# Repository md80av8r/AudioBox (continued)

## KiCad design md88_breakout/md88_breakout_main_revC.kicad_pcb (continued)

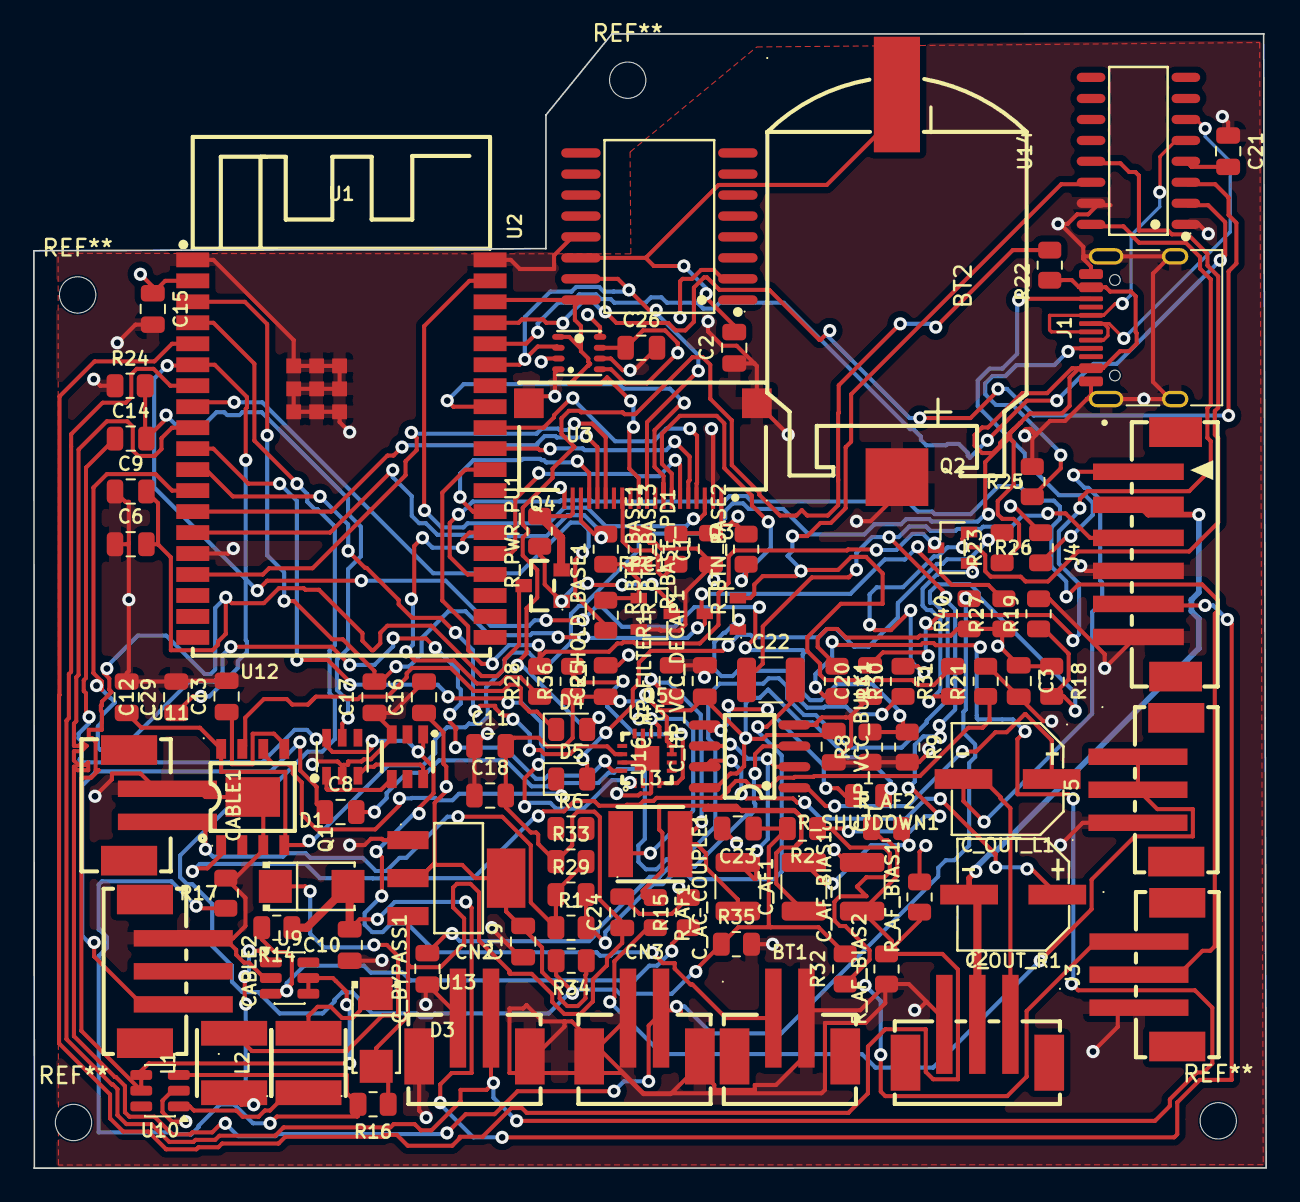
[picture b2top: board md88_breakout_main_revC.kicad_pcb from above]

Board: 4 copper layers, 74.6 x 68.7 mm, 108 parts (0 on the bottom side), 82 nets.

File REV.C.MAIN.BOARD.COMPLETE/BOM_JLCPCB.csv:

Comment,Designator,Footprint,LCSC Part #
18650_CELL,BT1,CONN-SMD_B2B-PH-SM4-TB-LF-SN,C160352
100nF,"C1,C2,C3,C14,C16,C20,C21,C23,C25,C26,C29,C_HP_VCC_DECAP1",C_0805_2012Metric,C49678
10uF,"C6,C9,C12,C13,C18,C_HP_VCC_BULK1",C_0805_2012Metric,C15850
1uF,"C8,C17,C_BYPASS1",C_0805_2012Metric,C28323
22uF,"C10,C11,C15,C19,C24",C_0805_2012Metric,C45783
10uF,"C22,C_AC_COUPLE1,C_AF1",C_1210_3225Metric,
MIC_PIGTAIL_0206,CABLE1,CONN-SMD_B2B-PH-SM4-TB-LF-SN,C160352
AUDIO_PIGTAIL_QUARTER_INCH,CABLE2,CONN-SMD_B3B-PH-SM4-TB-LF-SN,C160353
B2B-PH-SM4-TB,"CN2,CN3",CONN-SMD_B2B-PH-SM4-TB-LF-SN,C160352
100nF,C_AF_BIAS1,C_1210_3225Metric,
1nF,C_HP_FILTER1,C_0805_2012Metric,C46653
PM101M025E077PTR,"C_OUT_L1,C_OUT_R1",CAP-SMD_BD6.3-L6.6-W6.6-LS7.2-FD,C2858382
SS24,"D1,D3",SMA_L4.3-W2.6-LS5.2-RD,C50645
LED_CHRG_RED,D4,LED_0805_2012Metric,
LED_CHRG_GREEN,D5,LED_0805_2012Metric,
FH28K-20S-0.5SH,FPC1,CONN-SMD_FH28K-20S-0.5SH,C3168665
USB_C_POWER,J1,USB_C_Receptacle_HRO_TYPE-C-31-M-12,C165948
AUDIO_OUT_QUARTER_INCH,J2,CONN-SMD_B3B-PH-SM4-TB-LF-SN,C160353
MIC_OUT_0206,J3,CONN-SMD_B3B-PH-SM4-TB-LF-SN,C160353
LEMO_6PIN_PROFLIGHT,J4,CONN-SMD_6P-P2.00_B6B-PH-SM4-TB-LF-SN,C471518
AUX_IN_3.5MM,J5,CONN-SMD_B3B-PH-SM4-TB-LF-SN,C160353
4.7uH,"L1,L2",IND-SMD_L4.0-W4.0_LQH44PN2R2MP0L,C135263
SMNR4020-10UH,L3,IND-SMD_L4.0-W4.0_LQH44PN2R2MP0L,C135263
FS8205A_C2830320,Q1,SOT-23-6_L2.9-W1.6-P0.95-LS2.8-BR,C2830320
MMBT3904-C20526,"Q2,Q3,Q5",SOT-23-3_L2.9-W1.3-P1.90-LS2.4-BR,C20526
AO3401A,Q4,SOT-23_L2.9-W1.3-P1.90-LS2.4-BR,C15127
4.7k,"R1,R29",R_0805_2012Metric,C17673
10k,"R2,R15,R21,R27,R28,R30,R31,R32,R33,R40,R41,R_AF1,R_AF2,R_BASE_PD1,R_BTN_BASE1,R_BTN_BASE2,R_BTN_BASE3,R_HOLD_BASE1,R_PWR_PU1",R_0805_2012Metric,C17414
470,R6,R_0805_2012Metric,C17710
100k,"R8,R9,R18,R19,R34,R35,R36,R_AF_BIAS1,R_AF_BIAS2,R_SHUTDOWN1",R_0805_2012Metric,C17407
180k,R14,R_0805_2012Metric,C22827
200k,R16,R_0805_2012Metric,C17539
27k,R17,R_0805_2012Metric,C17593
1k,"R22,R23",R_0805_2012Metric,C17513
100,R24,R_0805_2012Metric,C17408
5.1k,"R25,R26",R_0805_2012Metric,C27834
ESP32-WROVER-E-N8R8,U1,WIFI-SMD_ESP32-WROVER-IE8MB,C2973667
DS3231SN#_C722469,U2,SOIC-16_L10.3-W7.5-P1.27-LS10.3-BL,C722469
BME280,U3,LGA-8_BME280_BL,C92489
MT3608,"U9,U10",SOT-23-6,
TP4056,U11,ESOP-8_L4.9-W3.9-P1.27-LS6.0-BL-EP,C16581
DW01A_C351410,U12,SOT-23-6_L2.9-W1.6-P0.95-LS2.8-BL,C351410
AMS1117-3.3,U13,SOT-223-3_L6.5-W3.4-P2.30-LS7.0-BR,C6186
CH340C_C7464026,U14,SOP-16_L10.0-W3.9-P1.27-LS6.0-BL,C7464026
MAX98357AETE+T,U15,TQFN-16_L3.0-W3.0-P0.50-BL-EP1.5,C910544
TPA6111A2DR,U16,SOIC-8_L5.0-W4.0-P1.27-LS6.0-BL,C497472

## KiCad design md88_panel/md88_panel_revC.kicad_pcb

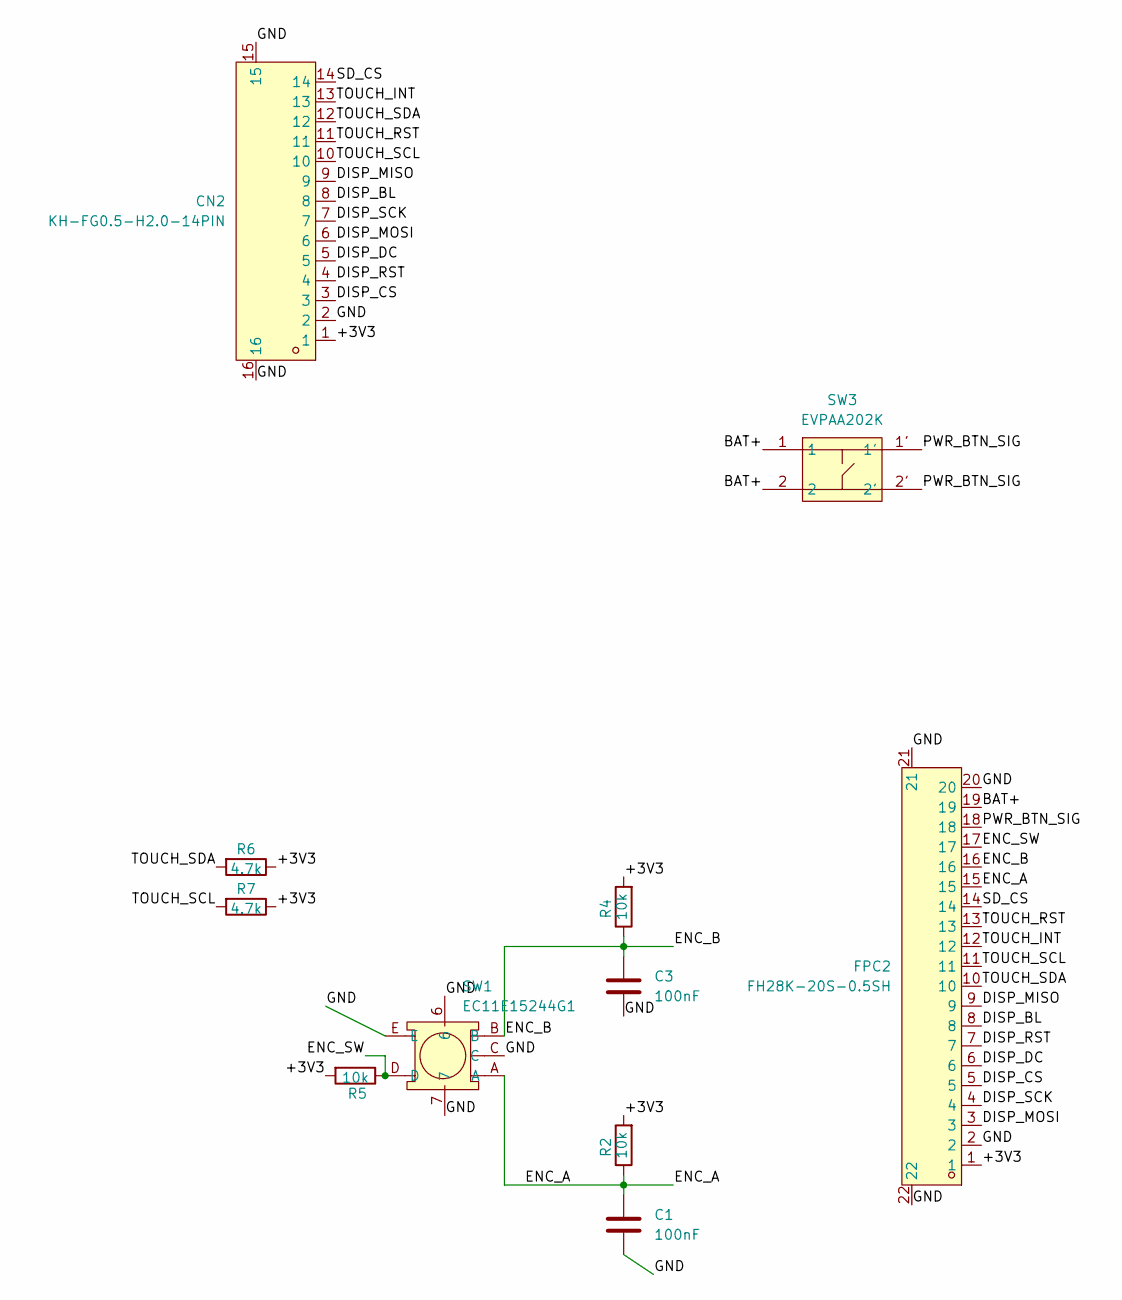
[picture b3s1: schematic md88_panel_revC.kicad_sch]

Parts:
C1, C3: 100nF; C_0805_2012Metric
CN2: KH-FG0.5-H2.0-14PIN; FPC-SMD_KH-FG0.5-H2.0-14PIN; MPN KH-FG0.5-H2.0-14PIN; LCSC Part C2797208
FPC2: FH28K-20S-0.5SH; CONN-SMD_FH28K-20S-0.5SH; MPN FH28K-20S-0.5SH; LCSC Part C3168665
R2, R4, R5: 10k; R_0805_2012Metric
R6, R7: 4.7k; R_0805_2012Metric
SW1: EC11E15244G1; SW-TH_EC11E15244G1; MPN EC11E15244G1; LCSC Part C370970
SW3: EVPAA202K; KEY-SMD_4P-L3.5-W2.9-P1.48-LS4.3-TL; MPN EVPAA202K; LCSC Part C79147

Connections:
/+3V3: CN2.1, FPC2.1, R2.2, R4.2, R5.2, R6.1, R7.1
/BAT+: FPC2.19, SW3.1, SW3.2
/DISP_BL: CN2.8, FPC2.8
/DISP_CS: CN2.3, FPC2.5
/DISP_DC: CN2.5, FPC2.6
/DISP_MISO: CN2.9, FPC2.9
/DISP_MOSI: CN2.6, FPC2.3
/DISP_RST: CN2.4, FPC2.7
/DISP_SCK: CN2.7, FPC2.4
/ENC_A: C1.1, FPC2.15, R2.1, SW1.A
/ENC_B: C3.1, FPC2.16, R4.1, SW1.B
/ENC_SW: FPC2.17, R5.1, SW1.D
/GND: C1.2, C3.2, CN2.2, CN2.15, CN2.16, FPC2.2, FPC2.20, FPC2.21, FPC2.22, SW1.6, SW1.7, SW1.C, SW1.E
/PWR_BTN_SIG: FPC2.18, SW3.1', SW3.2'
/SD_CS: CN2.14, FPC2.14
/TOUCH_INT: CN2.13, FPC2.12
/TOUCH_RST: CN2.11, FPC2.13
/TOUCH_SCL: CN2.10, FPC2.11, R7.2
/TOUCH_SDA: CN2.12, FPC2.10, R6.2

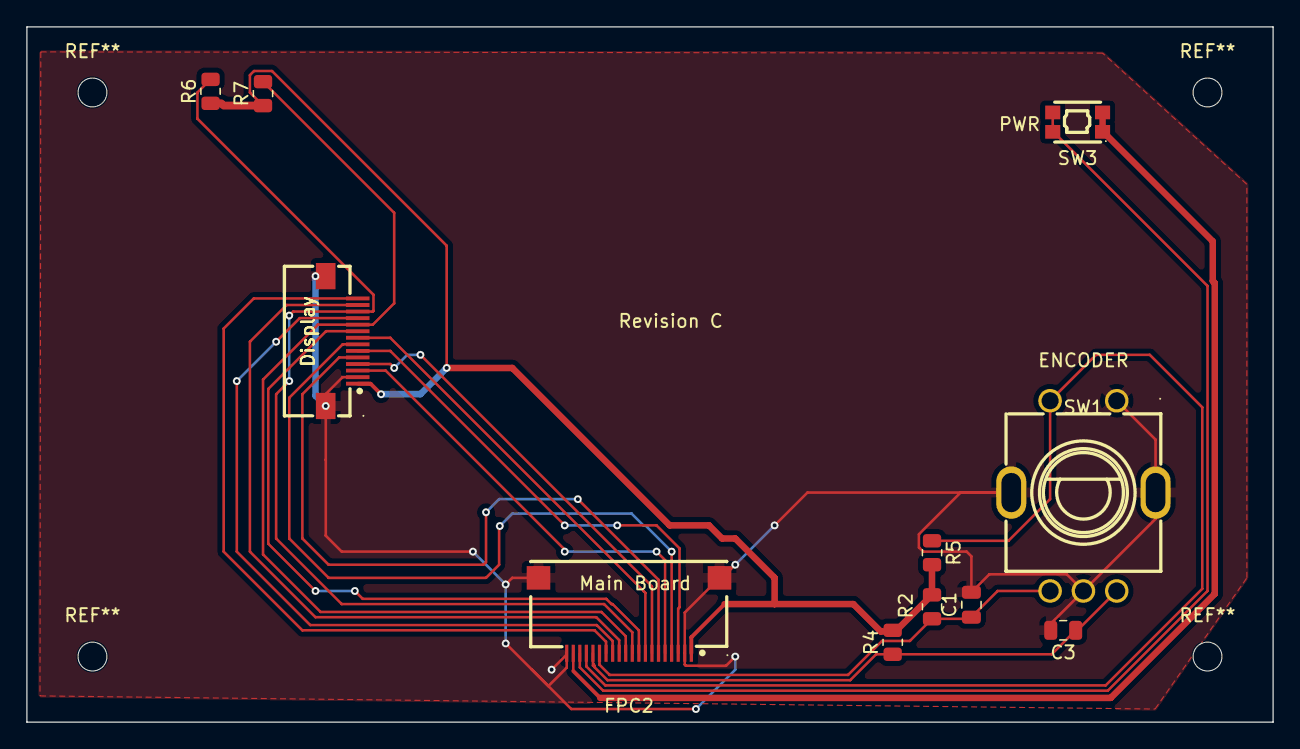
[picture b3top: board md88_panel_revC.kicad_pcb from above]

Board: 2 copper layers, 95.0 x 53.0 mm, 11 parts (0 on the bottom side), 19 nets.

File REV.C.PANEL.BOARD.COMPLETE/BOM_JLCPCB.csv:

Comment,Designator,Footprint,LCSC Part #
100nF,"C1,C3",C_0805_2012Metric,C49678
KH-FG0.5-H2.0-14PIN,CN2,FPC-SMD_KH-FG0.5-H2.0-14PIN,C2797208
FH28K-20S-0.5SH,FPC2,CONN-SMD_FH28K-20S-0.5SH,C3168665
10k,"R2,R4,R5",R_0805_2012Metric,C17414
4.7k,"R6,R7",R_0805_2012Metric,C17673
EC11E15244G1,SW1,SW-TH_EC11E15244G1,C370970
EVPAA202K,SW3,KEY-SMD_4P-L3.5-W2.9-P1.48-LS4.3-TL,C79147

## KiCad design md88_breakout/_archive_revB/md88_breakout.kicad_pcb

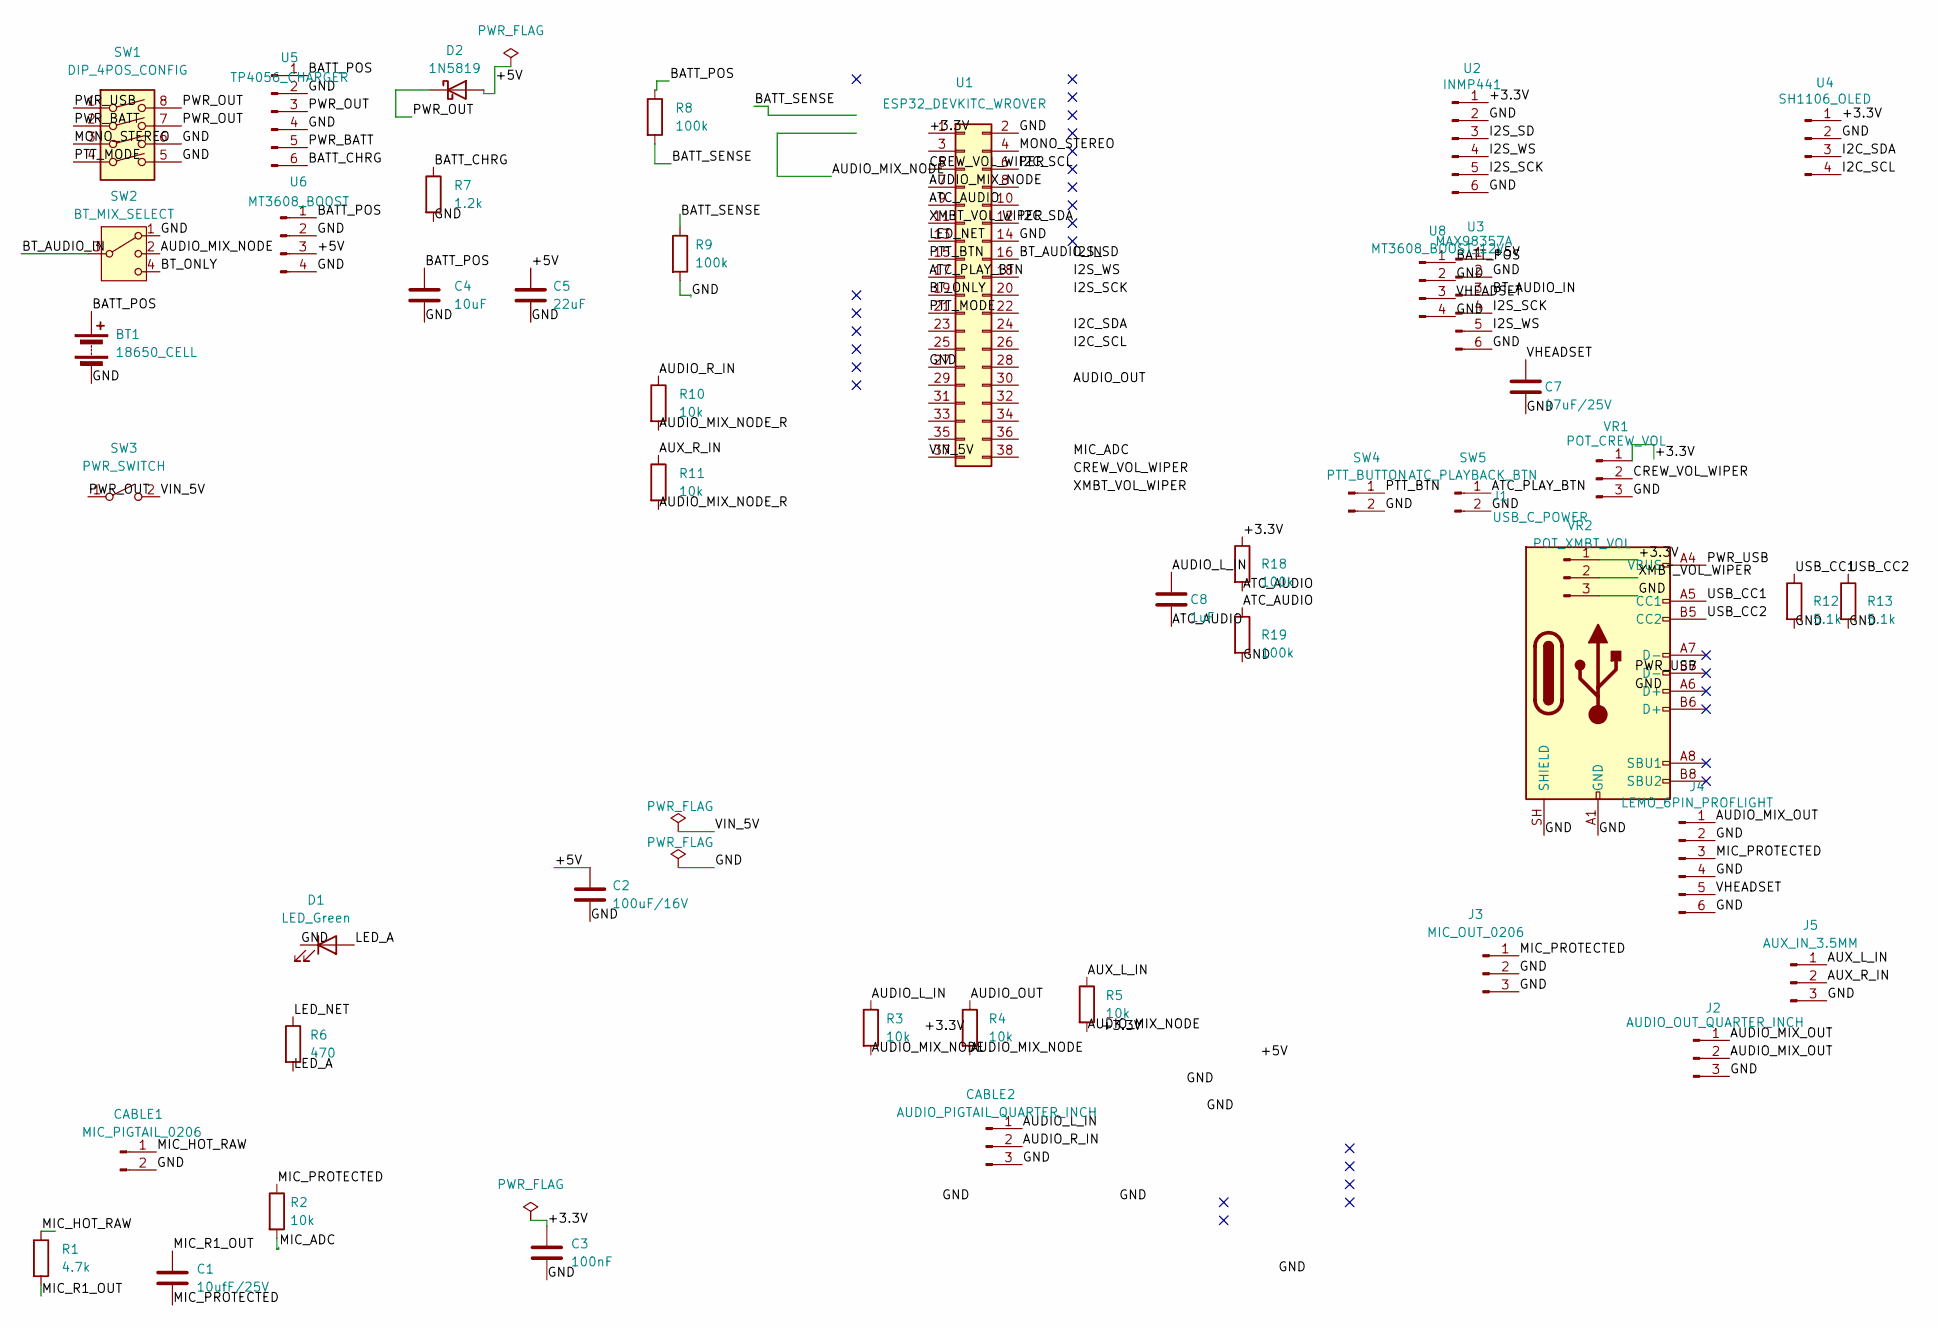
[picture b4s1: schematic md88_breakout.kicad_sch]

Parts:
BT1: 18650_CELL; BatteryHolder_Keystone_1042_1x18650
C1: 10ufF/25V; CP_Radial_D5.0mm_P2.00mm
C2: 100uF/16V; CP_Radial_D6.3mm_P2.50mm
C3: 100nF; C_0805_2012Metric
C4: 10uF; CP_Radial_D5.0mm_P2.00mm
C5: 22uF; CP_Radial_D6.3mm_P2.50mm
C7: 47uF/25V; CP_Radial_D6.3mm_P2.50mm
C8: 1uF; C_0805_2012Metric
CABLE1: MIC_PIGTAIL_0206; JST_PH_B2B-PH-K_1x02_P2.00mm_Vertical
CABLE2: AUDIO_PIGTAIL_QUARTER_INCH; JST_PH_B3B-PH-K_1x03_P2.00mm_Vertical
D1: LED_Green; LED_D3.0mm
D2: 1N5819; D_DO-41_SOD81_P10.16mm_Horizontal
J1: USB_C_POWER; USB_C_Receptacle_GCT_USB4105-xx-A_16P_TopMnt_Horizontal
J2: AUDIO_OUT_QUARTER_INCH; PinHeader_1x03_P2.54mm_Vertical
J3: MIC_OUT_0206; PinHeader_1x03_P2.54mm_Vertical
J4: LEMO_6PIN_PROFLIGHT; PinHeader_1x06_P2.54mm_Vertical
J5: AUX_IN_3.5MM; PinHeader_1x03_P2.54mm_Vertical
R1: 4.7k; R_0805_2012Metric
R2, R3, R4, R5, R10, R11: 10k; R_0805_2012Metric
R6: 470; R_0805_2012Metric
R7: 1.2k; R_Axial_DIN0207_L6.3mm_D2.5mm_P10.16mm_Horizontal
R8, R9, R18, R19: 100k; R_0805_2012Metric
R12, R13: 5.1k; R_0805_2012Metric
SW1: DIP_4POS_CONFIG; SW_DIP_SPSTx04_Slide_9.78x12.34mm_W7.62mm_P2.54mm
SW2: BT_MIX_SELECT; SW_SP3T_PCM13
SW3: PWR_SWITCH; SW_DIP_SPSTx01_Slide_6.7x4.1mm_W7.62mm_P2.54mm_LowProfile
SW4: PTT_BUTTON; PinHeader_1x02_P2.54mm_Vertical
SW5: ATC_PLAYBACK_BTN; PinHeader_1x02_P2.54mm_Vertical
U1: ESP32_DEVKITC_WROVER; ESP32_DevKitC_V4
U2: INMP441; PinHeader_1x06_P2.54mm_Vertical
U3: MAX98357A; PinHeader_1x06_P2.54mm_Vertical
U4: SH1106_OLED; PinHeader_1x04_P2.54mm_Vertical
U5: TP4056_CHARGER; PinHeader_1x06_P2.54mm_Vertical
U6: MT3608_BOOST; PinHeader_1x04_P2.54mm_Vertical
U8: MT3608_BOOST_12V; PinHeader_1x04_P2.54mm_Vertical
VR1: POT_CREW_VOL; Potentiometer_Alps_RK09K_Single_Vertical
VR2: POT_XMBT_VOL; Potentiometer_Alps_RK09K_Single_Vertical

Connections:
/+3.3V: C3.1, R18.1, U1.1, U2.1, U4.1, VR1.1, VR2.1
/+5V: C2.1, C5.1, D2.2 (A), U3.1, U6.3
/ATC_AUDIO: C8.2, R18.2, R19.1, U1.9
/ATC_PLAY_BTN: SW5.1, U1.17
/AUDIO_L_IN: C8.1, CABLE2.1, R3.1
/AUDIO_MIX_NODE: R3.2, R4.2, R5.2, SW2.2, U1.7
/AUDIO_MIX_NODE_R: R10.2, R11.2
/AUDIO_MIX_OUT: J2.1, J2.2, J4.1
/AUDIO_OUT: R4.1
/AUDIO_R_IN: CABLE2.2, R10.1
/AUX_L_IN: J5.1, R5.1
/AUX_R_IN: J5.2, R11.1
/BATT_CHRG: R7.1, U5.6
/BATT_POS: BT1.1 (+), C4.1, R8.1, U5.1, U6.1, U8.1
/BATT_SENSE: R8.2, R9.1
/BT_AUDIO_IN: SW2.3, U1.16, U3.3
/BT_ONLY: SW2.4, U1.19
/CREW_VOL_WIPER: U1.5, VR1.2
/GND: BT1.2 (-), C2.2, C3.2, C4.2, C5.2, C7.2, CABLE1.2, CABLE2.3, D1.1 (K), J1.A1 (GND), J1.A12 (GND), J1.B1 (GND), J1.B12 (GND), J1.SH (SHIELD), J2.3, J3.2, J3.3, J4.2, J4.4, J4.6, J5.3, R7.2, R9.2, R12.2, R13.2, R19.2, SW1.5, SW1.6, SW2.1, SW4.2, SW5.2, U1.2, U1.14, U1.27, U2.2, U2.6, U3.2, U3.6, U4.2, U5.2, U5.4, U6.2, U6.4, U8.2, U8.4, VR1.3, VR2.3
/I2C_SCL: U1.6, U4.4
/I2C_SDA: U1.12, U4.3
/I2S_SCK: U2.5, U3.4
/I2S_SD: U2.3
/I2S_WS: U2.4, U3.5
/LED_A: D1.2 (A), R6.2
/LED_NET: R6.1, U1.13
/MIC_ADC: R2.2
/MIC_HOT_RAW: CABLE1.1, R1.1
/MIC_PROTECTED: C1.2, J3.1, J4.3, R2.1
/MIC_R1_OUT: C1.1, R1.2
/MONO_STEREO: SW1.3, U1.4
/PTT_BTN: SW4.1, U1.15
/PTT_MODE: SW1.4, U1.21
/PWR_BATT: SW1.2, U5.5
/PWR_OUT: D2.1 (K), SW1.7, SW1.8, SW3.1 (A), U5.3
/PWR_USB: J1.A4 (VBUS), J1.A9 (VBUS), J1.B4 (VBUS), J1.B9 (VBUS), SW1.1
/USB_CC1: J1.A5 (CC1), R12.1
/USB_CC2: J1.B5 (CC2), R13.1
/VHEADSET: C7.1, J4.5, U8.3
/VIN_5V: SW3.2 (B), U1.37
/XMBT_VOL_WIPER: U1.11, VR2.2

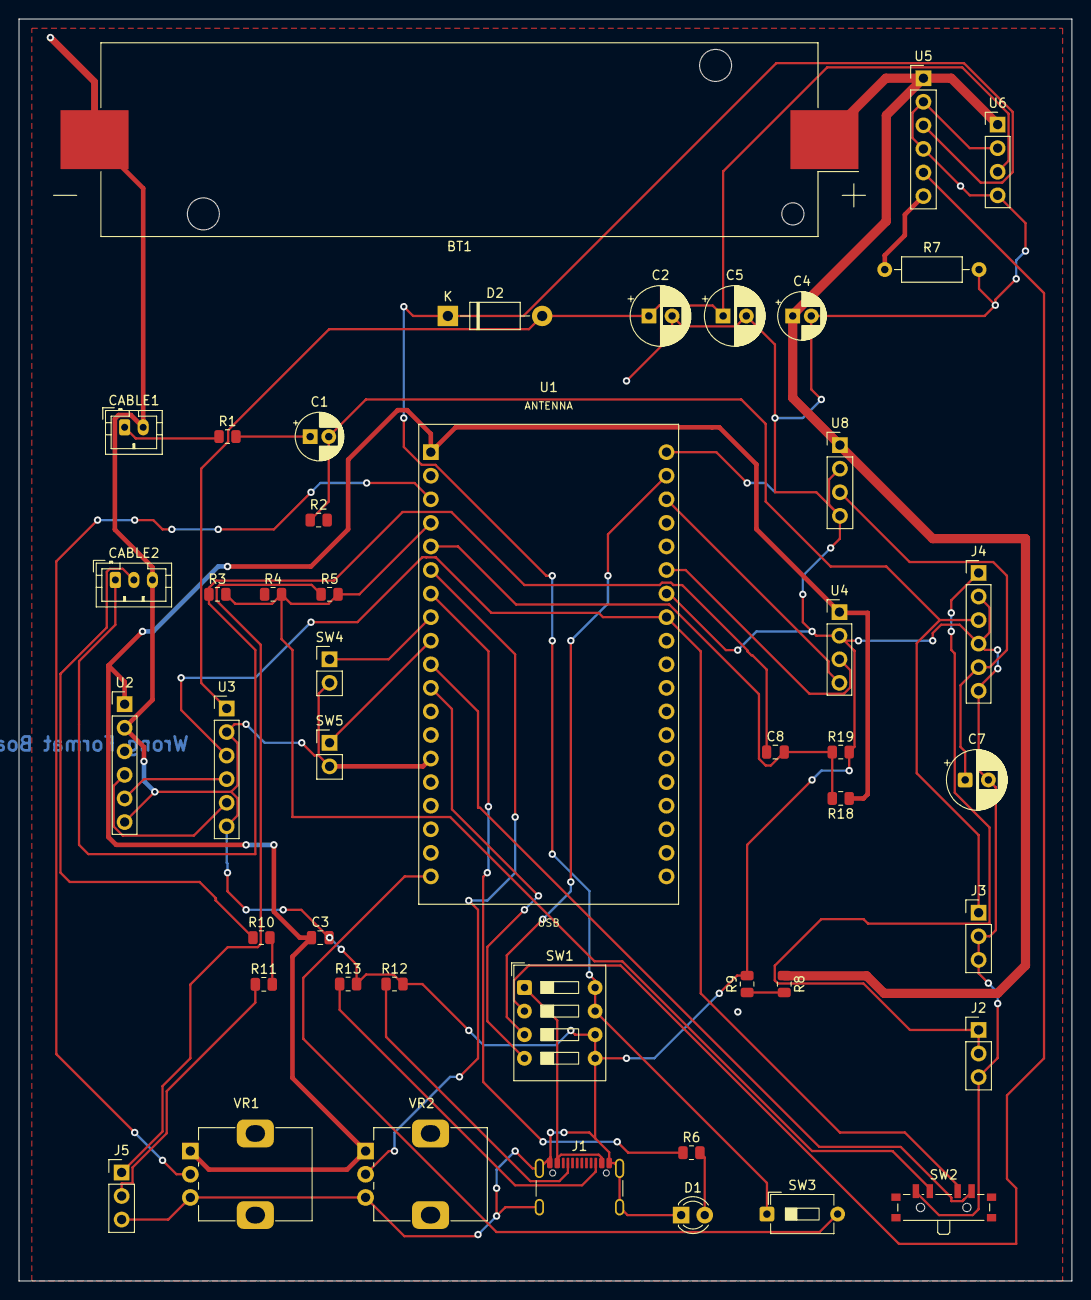
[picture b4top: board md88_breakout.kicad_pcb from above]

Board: 2 copper layers, 113.5 x 136.0 mm, 46 parts (0 on the bottom side), 38 nets.

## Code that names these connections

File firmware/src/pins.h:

// pins.h — MD-88 rev C GPIO assignments
// Locked from the schematic. Do not rebind without updating hardware.
#pragma once

// ─── Display (SPI, panel daughter board via FFC) ─────────────
#define PIN_DISP_MOSI   23
#define PIN_DISP_SCK    18
#define PIN_DISP_CS      5
#define PIN_DISP_DC      2
#define PIN_DISP_RST    -1   // tied to EN, no pin
#define PIN_DISP_BL     19   // backlight PWM
#define PIN_DISP_MISO   -1   // not connected (write-only display)

// ─── Touch (I2C, panel) ──────────────────────────────────────
#define PIN_TOUCH_SDA   21
#define PIN_TOUCH_SCL   22
#define PIN_TOUCH_INT   -1   // not connected — polled
#define PIN_TOUCH_RST   -1   // tied to EN

// ─── I2S audio out (to MAX98357A amp) ────────────────────────
#define PIN_I2S_BCLK    27
#define PIN_I2S_WS      26
#define PIN_I2S_DOUT    25

// ─── Encoder (EC11 on panel) ─────────────────────────────────
#define PIN_ENC_A       13
#define PIN_ENC_B       14
#define PIN_ENC_SW       4

// ─── Buttons ─────────────────────────────────────────────────
#define PIN_PWR_BTN     12   // momentary, debounced
#define PIN_PWR_HOLD    32   // drives Q5 — keeps soft-latch on
#define PIN_PTT_BTN     35   // input-only pin
#define PIN_ATC_BTN     33

// ─── Audio level monitoring (ADC) ────────────────────────────
#define PIN_MIC_ADC     36   // input-only — INMP441 level sense
#define PIN_AIRFRAME_ADC 39  // input-only — airframe audio level

// ─── Battery sense ───────────────────────────────────────────
#define PIN_BATT_SENSE  34   // input-only — LiPo voltage divider

// ─── Misc ────────────────────────────────────────────────────
#define PIN_J3_DETECT   15   // headset jack-detect

// ─── UART (USB-C via CH340C, auto-reset) ─────────────────────
// Pins 1 (TX) and 3 (RX) — used by Serial, no need to define

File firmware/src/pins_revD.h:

// pins_revD.h — MD-88 rev D GPIO assignments (ESP32-S3-WROOM-1-N16R8 / LCSC C2913202)
//
// Status: CORRECTED — earlier draft used GPIO 33-37 which are NOT available on this
// module variant (33-34 not broken out; 35-37 used by internal Octal flash for N16).
//
// Source of truth: /Users/jeffreykadans/Developer/MicBreakoutBoxrev_C/REV_D_PINMAP.md
//
// Debug serial: this design uses USB-CDC (over the native USB port) for `Serial.print()`.
// UART0 pins (GPIO 43/44) are repurposed for buttons because we don't need UART for
// debug — USB-CDC works whenever a USB host is connected.
//
#pragma once

// ──────────────────────────────────────────────────────────────
// USB (hardware-fixed — DO NOT REASSIGN)
// ──────────────────────────────────────────────────────────────
#define PIN_USB_DM            19   // USB D-
#define PIN_USB_DP            20   // USB D+

// ──────────────────────────────────────────────────────────────
// Power latch (must boot HIGH so soft-latch stays engaged)
// ──────────────────────────────────────────────────────────────
#define PIN_PWR_HOLD           0   // Output HIGH = stay on. Boot strap (pulled high by default) is compatible.

// ──────────────────────────────────────────────────────────────
// I2S audio bus
// ──────────────────────────────────────────────────────────────
#define PIN_I2S_BCLK           5
#define PIN_I2S_WS             6
#define PIN_I2S_DOUT           7
#define PIN_I2S_DIN           15

// ──────────────────────────────────────────────────────────────
// Shared SPI bus (display + SD card)
// ──────────────────────────────────────────────────────────────
#define PIN_SPI_MOSI          11
#define PIN_SPI_MISO          13
#define PIN_SPI_SCK           12

#define PIN_DISP_CS           10
#define PIN_DISP_DC           14
#define PIN_DISP_RST           8
#define PIN_DISP_BL           16

#define PIN_SD_CS              9

// ──────────────────────────────────────────────────────────────
// Shared I2C bus (touch + BME280 + DS3231 + FUSB302)
// ──────────────────────────────────────────────────────────────
#define PIN_I2C_SDA           17
#define PIN_I2C_SCL           18

// Note: no hardware interrupt pins. FUSB302, touch, and RTC are all polled via I2C.
// PD events check every 50ms, touch every 30ms.

// ──────────────────────────────────────────────────────────────
// LEDs
// ──────────────────────────────────────────────────────────────
#define PIN_LED_STATUS         2   // Boot / error / general status
#define PIN_LED_PTT_ACTIVE    21   // Lit when local PTT keyed

// ──────────────────────────────────────────────────────────────
// Buttons + encoder + headset detect
// ──────────────────────────────────────────────────────────────
#define PIN_PWR_BTN           43   // Was UART TX. Input pullup; HIGH at boot = normal boot
#define PIN_PTT_BTN           44   // Was UART RX. Input pullup
#define PIN_ATC_BTN           38
#define PIN_ENC_A             39
#define PIN_ENC_B             40
#define PIN_ENC_SW            41
#define PIN_J3_DETECT         42   // LOW = headset plugged in

// ──────────────────────────────────────────────────────────────
// ADC inputs (ADC1 only — ADC2 conflicts with WiFi)
// ──────────────────────────────────────────────────────────────
#define PIN_MIC_ADC            1   // ADC1_CH0
#define PIN_BATT_SENSE         3   // ADC1_CH2 — LiPo via ÷2 divider
#define PIN_AIRFRAME_ADC       4   // ADC1_CH3

// ──────────────────────────────────────────────────────────────
// Master/slave role DIP switch
// ──────────────────────────────────────────────────────────────
#define PIN_ROLE_DIP_0        47
#define PIN_ROLE_DIP_1        48
//   00 = SLAVE
//   01 = FO (backup master)
//   10 = CAPTAIN (master)
//   11 = reserved

// ──────────────────────────────────────────────────────────────
// NOT AVAILABLE on this module (do not try to use)
// ──────────────────────────────────────────────────────────────
// GPIO 22-25   — chip-level gap, don't exist
// GPIO 26-37   — internal SPI flash + PSRAM (N16R8 uses Octal flash → 33-37 occupied)
// GPIO 45      — VDD_SPI boot strap (must be LOW at boot)
// GPIO 46      — Boot ROM print strap (must be LOW at boot)

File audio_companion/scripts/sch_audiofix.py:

import re, uuid
P="/Users/jeffreykadans/Developer/MicBreakoutBox/REV_D/audio_companion_work/audio_companion.kicad_sch"
t=open(P).read()
U=lambda: str(uuid.uuid4())
def fmt(v): return ('%.4f'%v).rstrip('0').rstrip('.')
def sym_span(ref):
    for m in re.finditer(r'\n\t\(symbol\n\t\t\(lib_id "([^"]+)"\)\n\t\t\(at ([\d.\-]+) ([\d.\-]+) (\d+)\)',t):
        i=m.start()+1; j=t.find('\n\t(symbol\n',i+10); j=len(t) if j<0 else j+1
        if f'(property "Reference" "{ref}"' in t[i:j]: return i,j,float(m.group(2)),float(m.group(3))
    raise SystemExit("no symbol "+ref)
def rename_label(old,new,x,y):
    global t
    pat=re.compile(r'(\t\(label ")'+re.escape(old)+r'("\n\t\t\(at '+re.escape(fmt(x))+' '+re.escape(fmt(y))+r' \d+\))')
    assert len(pat.findall(t))==1,(old,x,y,len(pat.findall(t)))
    t=pat.sub(lambda m:m.group(1)+new+m.group(2),t,1)
def remove_label(name,x,y):
    global t
    pat=re.compile(r'\t\(label "'+re.escape(name)+r'"\n\t\t\(at '+re.escape(fmt(x))+' '+re.escape(fmt(y))+r' \d+\).*?\n\t\)\n',re.S)
    m=pat.search(t); assert m,("nolabel",name,x,y); t=t[:m.start()]+t[m.end():]
def remove_wire(x1,y1,x2,y2):
    global t
    for a,b in (((x1,y1),(x2,y2)),((x2,y2),(x1,y1))):
        pat=re.compile(r'\t\(wire\n\t\t\(pts\n\t\t\t\(xy '+re.escape(fmt(a[0]))+' '+re.escape(fmt(a[1]))+r'\) \(xy '+re.escape(fmt(b[0]))+' '+re.escape(fmt(b[1]))+r'\)\n\t\t\)\n.*?\n\t\)\n',re.S)
        m=pat.search(t)
        if m: t=t[:m.start()]+t[m.end():]; return
    raise SystemExit(("nowire",x1,y1,x2,y2))
def add_label(name,x,y,ang):
    global t
    just="left bottom" if ang in (0,90) else "right bottom"
    s=f'\t(label "{name}"\n\t\t(at {fmt(x)} {fmt(y)} {ang})\n\t\t(effects\n\t\t\t(font\n\t\t\t\t(size 1.27 1.27)\n\t\t\t)\n\t\t\t(justify {just})\n\t\t)\n\t\t(uuid "{U()}")\n\t)\n'
    k=t.index('\t(sheet_instances'); t=t[:k]+s+t[k:]
pwr_n=[max(int(x) for x in re.findall(r'"#PWR0*(\d+)"',t))]
def clone(src,newref,value,footprint,x,y,rot=None):
    global t
    i,j,sx,sy=sym_span(src); blk=t[i:j]; dx,dy=x-sx,y-sy
    blk=re.sub(r'\(at ([\-\d.]+) ([\-\d.]+)',lambda m:'(at %s %s'%(fmt(float(m.group(1))+dx),fmt(float(m.group(2))+dy)),blk)
    if rot is not None: blk=re.sub(r'(\t\t\(at [\-\d.]+ [\-\d.]+ )\d+\)',lambda m:m.group(1)+'%d)'%rot,blk,1)
    blk=re.sub(r'(\(property "Reference" ")[^"]*"',lambda m:m.group(1)+newref+'"',blk,1)
    blk=re.sub(r'(\(reference ")[^"]*"',lambda m:m.group(1)+newref+'"',blk)
    if value is not None: blk=re.sub(r'(\(property "Value" ")[^"]*"',lambda m:m.group(1)+value+'"',blk,1)
    if footprint is not None: blk=re.sub(r'(\(property "Footprint" ")[^"]*"',lambda m:m.group(1)+footprint+'"',blk,1)
    for ou in set(re.findall(r'\(uuid "([0-9a-f-]{36})"\)',blk)): blk=blk.replace(ou,U())
    for ou in set(re.findall(r'\(pin "[^"]+"\n\t\t\t\(uuid "([0-9a-f-]{36})"',blk)): blk=blk.replace(ou,U())
    t=t[:j]+blk+t[j:]
R0402="Resistor_SMD:R_0402_1005Metric"
def two_pin_vertical(newref,value,fp,x,y,top,bottom,src="R8",rot=0):
    # R8 is vertical rot 180 (pins at y+-3.81); we force rot 0 for polarized/cap templates handled by caller
    clone(src,newref,value,fp,x,y,rot)
    add_label(top,x,y-3.81,90); add_label(bottom,x,y+3.81,270)
# ---------------- TPA stage ----------------
rename_label("TPA_IN_L","TPA_IN_L_N",196.85,110.49)
rename_label("TPA_IN_R","TPA_IN_R_N",237.49,113.03)
rename_label("HP_L_AMP","HP_L_VO",194.31,106.68)
rename_label("HP_R_AMP","HP_R_VO",231.14,110.49)
# SHUTDOWN -> GND
remove_label("+3V3",231.14,115.57)
pwr_n[0]+=1; clone("#PWR011","#PWR%02d"%pwr_n[0],None,None,231.14,115.57,90)
# new parts, left channel row y=152, right channel row y=172 ; x spacing 14
for side,y in (("L",152.4),("R",172.72)):
    n=side
    two_pin_vertical(f"R-TPA-IN-{n}","10k",R0402,35.56,y,f"TPA_IN_{n}",f"TPA_IN_{n}_N",src="R8",rot=180)
    two_pin_vertical(f"R-TPA-FB-{n}","10k",R0402,48.26,y,f"HP_{n}_VO",f"TPA_IN_{n}_N",src="R8",rot=180)
    two_pin_vertical(f"C-HP-{n}","220uF 6.3V","Capacitor_Tantalum_SMD:CP_EIA-6032-28_Kemet-C",60.96,y,f"HP_{n}_VO",f"HP_{n}_CAP",src="C-BULK-3V3",rot=0)
    two_pin_vertical(f"R-HP-{n}","10R",R0402,73.66,y,f"HP_{n}_CAP",f"HP_{n}_AMP",src="R8",rot=180)
# ---------------- Mic preamp ----------------
remove_wire(227.33,207.01,227.33,242.57)
remove_wire(207.01,207.01,207.01,212.09)
remove_wire(207.01,212.09,209.55,212.09)
add_label("MIC_RAW",209.55,212.09,180)
rename_label("+3V3","MIC_BIAS_SRC",217.17,212.09)
# solder jumper (3V3 -> MIC_BIAS_SRC) from Conn_01x02 template
clone("J-HAPTIC-1","JP-MIC-BIAS","SolderJumper","Jumper:SolderJumper-2_P1.3mm_Open_Pad1.0x1.5mm",100.33,152.4,0)
add_label("+3V3",100.33-5.08,152.4,180); add_label("MIC_BIAS_SRC",100.33-5.08,152.4+2.54,180)
# series bias resistor
two_pin_vertical("R-MICBIAS","100k",R0402,114.3,152.4,"VMID_BIAS","MIC_IN_P",src="R8",rot=180)
add_label("MIC_IN_P",230.0,207.01,0)
# ---------------- ANR enable pull-down ----------------
remove_label("+3V3",334.01,140.97)
pwr_n[0]+=1; clone("#PWR011","#PWR%02d"%pwr_n[0],None,None,334.01,140.97,0)
open(P,"w").write(t); print("schematic edited")

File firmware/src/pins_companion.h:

// pins_companion.h — Audio Companion board GPIO assignments
// (Elecrow ESP32-S3 Advanced "Wireless module" header -> companion HDR-CP-L-1 / HDR-CP-R-1)
//
// Source: traced from production gerbers (audio_companion v7 Y15) and the
// Elecrow header silkscreen. Header columns read top to bottom.
//
// NOTE: GPIO19/20 are the ESP32-S3 native USB D-/D+ pins. Using them here
// disables USB-Serial/JTAG; flash over the Elecrow UART port instead.
//
#pragma once

// ──────────────────────────────────────────────────────────────
// I2S audio bus (ES8388 codec, U1)
// ──────────────────────────────────────────────────────────────
#define PIN_I2S_MCLK          19   // HDR-CP-L-1 pin 1
#define PIN_I2S_BCLK           5   // HDR-CP-R-1 pin 2
#define PIN_I2S_LRCK           6   // HDR-CP-R-1 pin 4
#define PIN_I2S_DOUT           4   // ESP out -> codec DAC in  (HDR-CP-R-1 pin 3)
#define PIN_I2S_DIN            2   // codec ADC out -> ESP in  (HDR-CP-L-1 pin 5)

// ──────────────────────────────────────────────────────────────
// I2C bus (ES8388, PCA9534 expander, DRV2605L haptic)
// ──────────────────────────────────────────────────────────────
#define PIN_I2C_SCL           16   // HDR-CP-L-1 pin 2
#define PIN_I2C_SDA           15   // HDR-CP-L-1 pin 3

// ──────────────────────────────────────────────────────────────
// Control outputs
// ──────────────────────────────────────────────────────────────
#define PIN_ANR_POWER_EN       8   // Enables MT3608 +12V boost (HDR-CP-L-1 pin 6)
#define PIN_BYPASS_EN         20   // Bypass enable, drives D5 LED (HDR-CP-R-1 pin 1)

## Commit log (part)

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2026-06-02 Initial commit — Rev C complete, Rev D architecture captured
    Rev C status:
    - Main board (4-layer) and panel board (2-layer) in production at JLC
    - Schematic bug fixes captured: BT1 power path, J4 Bose pinout, value typos
    - BT2 (CR2032) marked DNP — handled by hand-solder after delivery
    Rev D planning complete:
    - ESP32-S3-WROOM-1-N16R8 with native USB
